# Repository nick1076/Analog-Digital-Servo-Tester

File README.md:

# Analog-Digital-Servo-Tester
A repo for my Analog & Digital Servo Motor Tester board.

# Parts List
See the below link for the full DigiKey parts list:

https://www.digikey.com/en/mylists/list/5TK6GYXG6Z

# Board Files
See "PCBWay-Order-Files.zip", you can upload that directly on PCBWay's website to order the exact board. Also, the original gerbers are in the project directory.

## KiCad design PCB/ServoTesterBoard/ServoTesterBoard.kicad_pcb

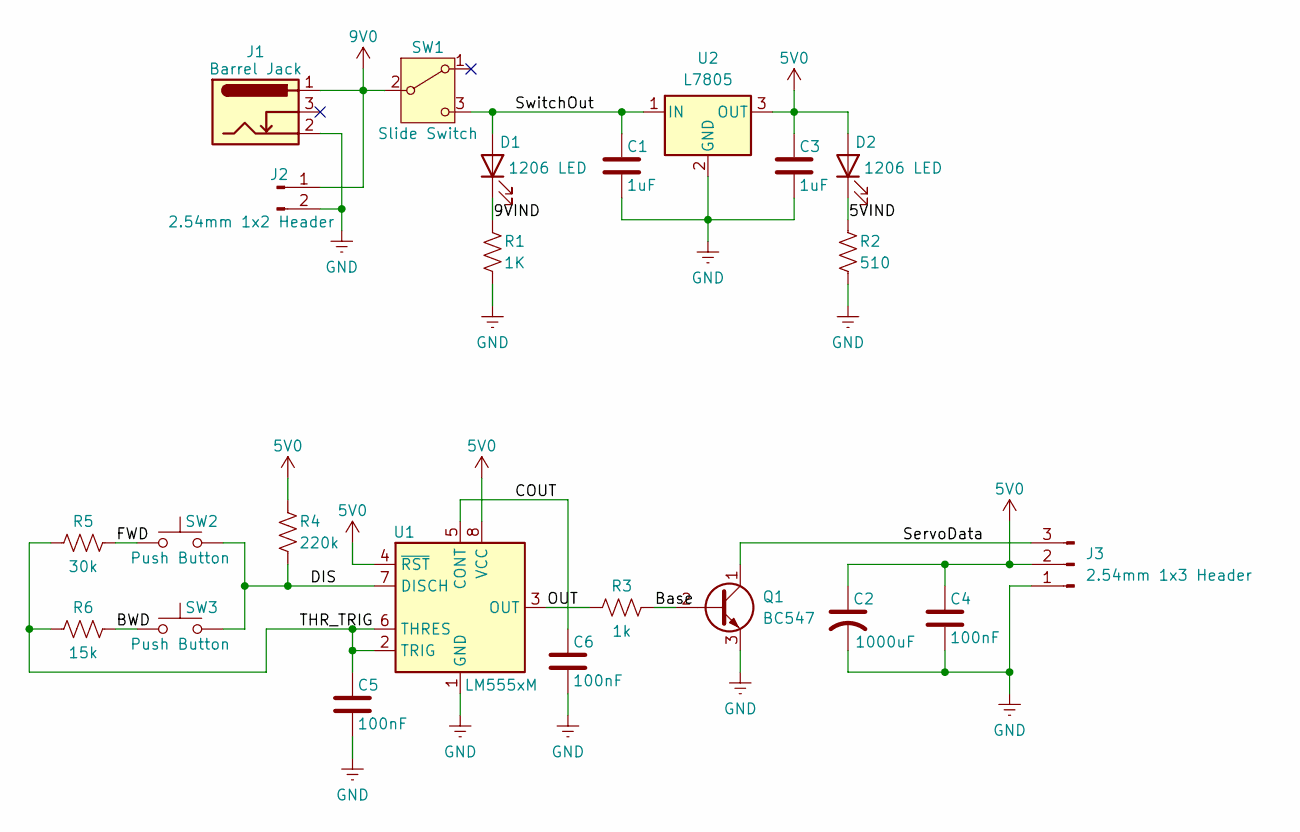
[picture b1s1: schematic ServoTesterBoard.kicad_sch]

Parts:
C1, C3: 1uF; C_1206_3216Metric
C2: 1000uF; CP_Radial_D10.0mm_P5.00mm
C4, C5, C6: 100nF; C_1206_3216Metric
D1, D2: 1206 LED; LED_1206_3216Metric
J1: Barrel Jack; BarrelJack_GCT_DCJ200-10-A_Horizontal
J2: 2.54mm 1x2 Header; PinHeader_1x02_P2.54mm_Vertical
J3: 2.54mm 1x3 Header; PinHeader_1x03_P2.54mm_Vertical
Q1: BC547; TO-92_Inline
R1: 1K; R_1206_3216Metric_Pad1.30x1.75mm_HandSolder
R2: 510; R_1206_3216Metric_Pad1.30x1.75mm_HandSolder
R3: 1k; R_1206_3216Metric_Pad1.30x1.75mm_HandSolder
R4: 220k; R_1206_3216Metric_Pad1.30x1.75mm_HandSolder
R5: 30k; R_1206_3216Metric_Pad1.30x1.75mm_HandSolder
R6: 15k; R_1206_3216Metric_Pad1.30x1.75mm_HandSolder
SW1: Slide Switch; SW_Slide_SPDT_Straight_CK_OS102011MS2Q
SW2, SW3: Push Button; SW_PUSH_6mm
U1: LM555xM; SOIC-8_3.9x4.9mm_P1.27mm
U2: L7805; TO-220_STM

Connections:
5V0: C2.1, C3.1, C4.1, D2.2 (A), J3.2, R4.1, U1.4 (~RST), U1.8 (VCC), U2.3 (OUT); also elsewhere on the board
9V0: J1.1, J2.1, SW1.2 (B)
/5VIND: D2.1 (K), R2.1
/9VIND: D1.1 (K), R1.1
/BWD: R6.2, SW3.1
/Base: Q1.2 (B), R3.2
/COUT: C6.1, U1.5 (CONT)
/DIS: R4.2, SW2.2, SW3.2, U1.7 (DISCH)
/FWD: R5.2, SW2.1
/OUT: R3.1, U1.3 (OUT)
/ServoData: J3.3, Q1.1 (C); also elsewhere on the board
/SwitchOut: C1.1, D1.2 (A), SW1.3 (C), U2.1 (IN)
/THR_TRIG: C5.1, R5.1, R6.1, U1.2 (TRIG), U1.6 (THRES)
GND: C1.2, C2.2, C3.2, C4.2, C5.2, C6.2, J1.2, J2.2, J3.1, Q1.3 (E), R1.2, R2.2, U1.1 (GND), U2.2 (GND)

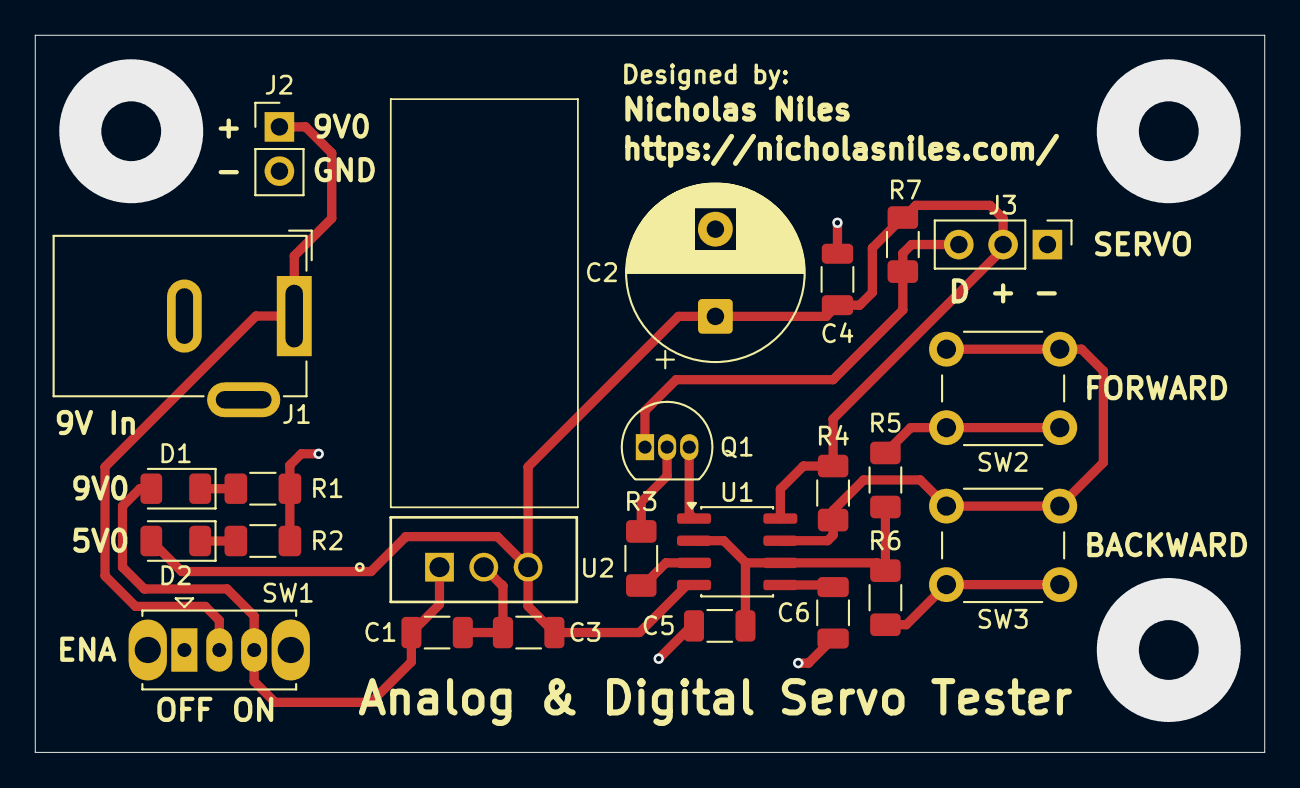
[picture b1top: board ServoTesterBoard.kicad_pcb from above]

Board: 2 copper layers, 70.5 x 41.1 mm, 24 parts (0 on the bottom side), 14 nets.

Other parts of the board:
R7: 470; R_1206_3216Metric_Pad1.30x1.75mm_HandSolder

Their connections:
5V0: R7.2; also elsewhere on the board
/ServoData: R7.1; also elsewhere on the board

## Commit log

2026-06-04 BTC Momentum chaser - done - now adding velocity
2026-06-07 Finished
2026-06-07 Finished files
